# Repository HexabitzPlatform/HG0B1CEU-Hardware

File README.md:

# HG0B1CEU-Hardware
Hexabitz STM32G0B1CEU6N DevKit Hardware Design

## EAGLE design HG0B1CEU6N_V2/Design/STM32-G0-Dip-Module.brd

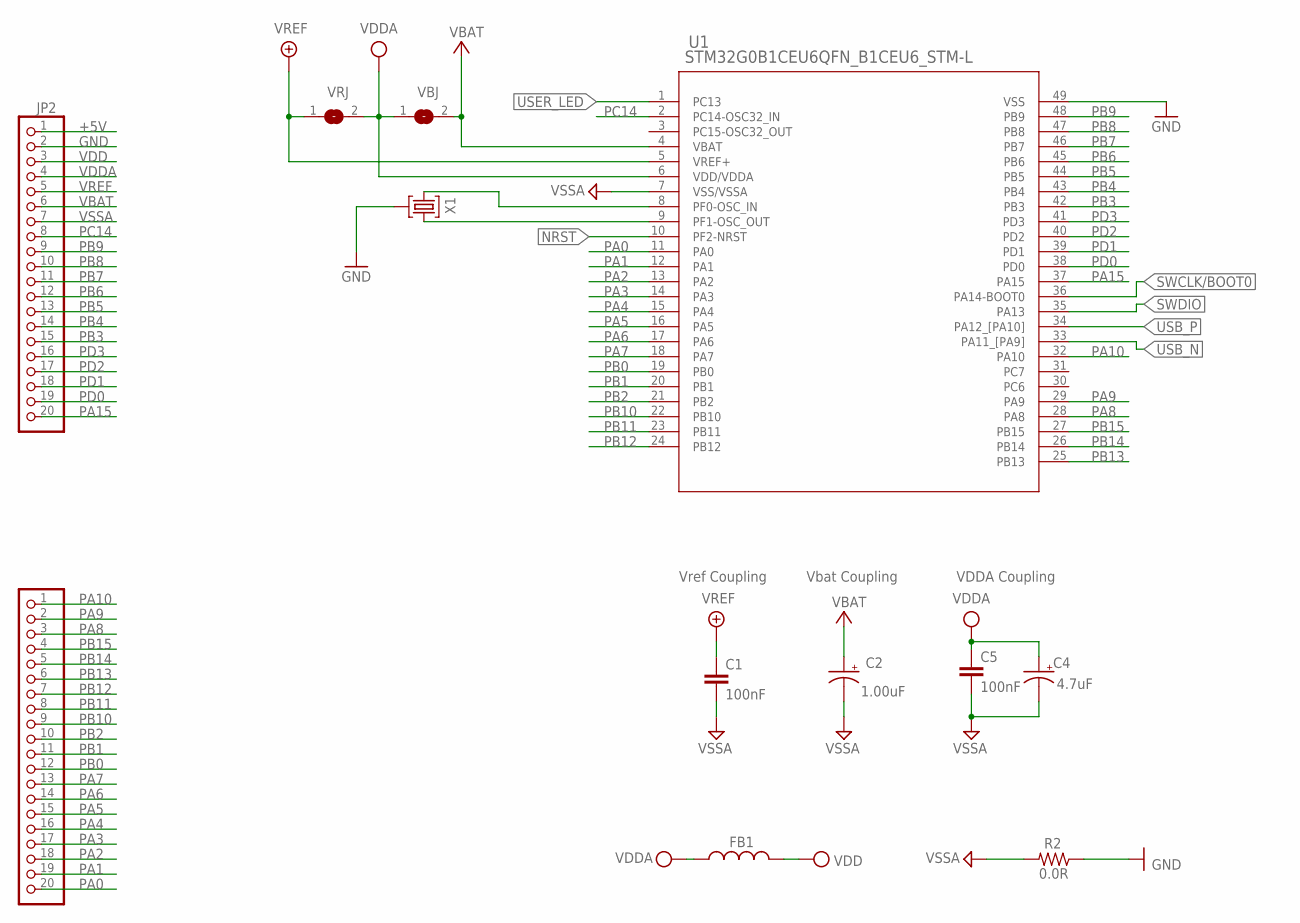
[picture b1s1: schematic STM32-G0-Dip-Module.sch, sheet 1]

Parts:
C1: 100nF; C-0603; TOLERANCE 10%; VOLTAGE_RATING 10V; MPN C0603C104K8RACTU
C2: 1.00uF; C-0805-POL; TOLERANCE 10%; VOLTAGE_RATING 16V; MPN CC0805KKX7R7BB105
C4: 4.7uF; C-0805-POL; TOLERANCE 10%; VOLTAGE_RATING 25V; MPN GRM21BC81E475KA12L
C5: 100nF; C-0603; TOLERANCE 10%; VOLTAGE_RATING 10; MPN C0603C104K8RACTU
FB1: FB-TDK_MMZ1608Y300B; MPN MMZ1608Y300B
JP1, JP2: PINHD-1X20; 1X20
R2: 0.0R; R-0603; MPN RC0603JR-070RL
U1: STM32G0B1CEU6QFN_B1CEU6_STM-L; QFN_B1CEU6_STM-L
VBJ: SJ
VRJ: SJ
X1: XTALL_CSTCE8M00G52

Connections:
+5V: JP2.1; also elsewhere on the board
CRYSTAL_N: U1.8 (PF0-OSC_IN), X1.P$1 (1)
CRYSTAL_P: U1.9 (PF1-OSC_OUT), X1.P$3 (3)
GND: JP2.2, R2.1, U1.49 (VSS), X1.P$2 (2); also elsewhere on the board
NRST: U1.10 (PF2-NRST); also elsewhere on the board
PA0: JP1.20, U1.11 (PA0)
PA1: JP1.19, U1.12 (PA1)
PA2: JP1.18, U1.13 (PA2)
PA3: JP1.17, U1.14 (PA3)
PA4: JP1.16, U1.15 (PA4)
PA5: JP1.15, U1.16 (PA5)
PA6: JP1.14, U1.17 (PA6)
PA7: JP1.13, U1.18 (PA7)
PA8: JP1.3, U1.28 (PA8)
PA9: JP1.2, U1.29 (PA9)
PA10: JP1.1, U1.32 (PA10)
PA15: JP2.20, U1.37 (PA15)
PB0: JP1.12, U1.19 (PB0)
PB1: JP1.11, U1.20 (PB1)
PB2: JP1.10, U1.21 (PB2)
PB3: JP2.15, U1.42 (PB3)
PB4: JP2.14, U1.43 (PB4)
PB5: JP2.13, U1.44 (PB5)
PB6: JP2.12, U1.45 (PB6)
PB7: JP2.11, U1.46 (PB7)
PB8: JP2.10, U1.47 (PB8)
PB9: JP2.9, U1.48 (PB9)
PB10: JP1.9, U1.22 (PB10)
PB11: JP1.8, U1.23 (PB11)
PB12: JP1.7, U1.24 (PB12)
PB13: JP1.6, U1.25 (PB13)
PB14: JP1.5, U1.26 (PB14)
PB15: JP1.4, U1.27 (PB15)
PC14: JP2.8, U1.2 (PC14-OSC32_IN)
PD0: JP2.19, U1.38 (PD0)
PD1: JP2.18, U1.39 (PD1)
PD2: JP2.17, U1.40 (PD2)
PD3: JP2.16, U1.41 (PD3)
SWCLK/BOOT0: U1.36 (PA14-BOOT0); also elsewhere on the board
SWDIO: U1.35 (PA13); also elsewhere on the board
USB_N: U1.33 (PA11_[PA9]); also elsewhere on the board
USB_P: U1.34 (PA12_[PA10]); also elsewhere on the board
USER_LED: U1.1 (PC13); also elsewhere on the board
VBAT: C2.1 (+), JP2.6, U1.4 (VBAT), VBJ.2
VDD: FB1.2, JP2.3; also elsewhere on the board
VDDA: C4.1 (+), C5.1, FB1.1, JP2.4, U1.6 (VDD/VDDA), VBJ.1, VRJ.2
VREF: C1.1, JP2.5, U1.5 (VREF+), VRJ.1
VSSA: C1.2, C2.2 (-), C4.2 (-), C5.2, JP2.7, R2.2, U1.7 (VSS/VSSA)

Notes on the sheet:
VDDA Coupling
Vref Coupling
Vbat Coupling

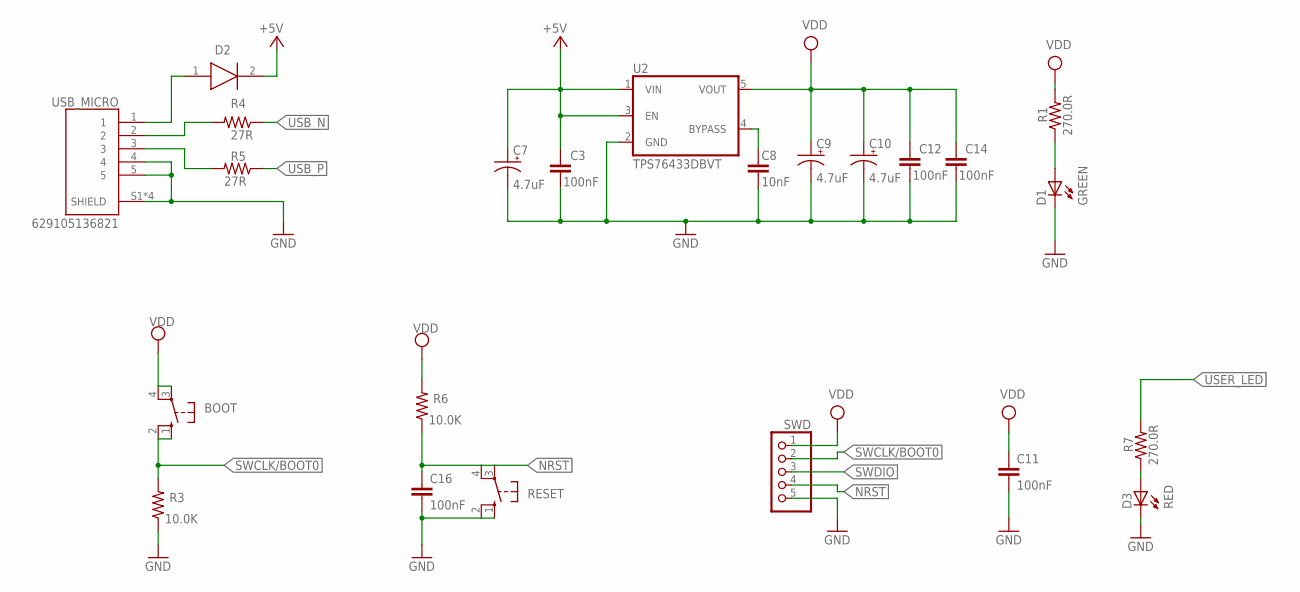
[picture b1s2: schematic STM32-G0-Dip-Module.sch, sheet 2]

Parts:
BOOT: 10-XX; B3F-10XX
C3, C12, C14: 100nF; C-0603; TOLERANCE 10%; VOLTAGE_RATING 10; MPN C0603C104K8RACTU
C7, C9, C10: 4.7uF; C-0805-POL; TOLERANCE 10%; VOLTAGE_RATING 25V; MPN GRM21BC81E475KA12L
C8: 10nF; C-0603; TOLERANCE 10%; VOLTAGE_RATING 10; MPN C0603C104K8RACTU
C11, C16: 100nF; C-0603; TOLERANCE 10%; VOLTAGE_RATING 10V; MPN C0603C104K8RACTU
D1: GREEN; VLMS1300-GS08; MPN VLMS1300-GS08
D2: FSM17PL-TP
D3: RED; VLMS1300-GS08; MPN VLMS1300-GS08
R1, R7: 270.0R; R-0603; TOLERANCE 1%; MPN RC0603FR-07270RL
R3, R6: 10.0K; R-0603; TOLERANCE 5%; MPN RC0603JR-0710KL
R4, R5: 27R; R-0603; TOLERANCE 5%; MPN RC0603JR-0710KL
RESET: 10-XX; B3F-10XX
SWD: PINHD-1X5/90; 1X05/90
U2: TPS76433DBVT; SOT25
USB_MICRO: 629105136821; WE_629105136821

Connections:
+5V: C3.1, C7.1 (+), D2.2 (K), U2.1 (VIN), U2.3 (EN); also elsewhere on the board
D_N: R4.2, USB_MICRO.2
D_P: R5.2, USB_MICRO.3
GND: C3.2, C7.2 (-), C8.2, C9.2 (-), C10.2 (-), C11.2, C12.2, C14.2, C16.2, D1.C, D3.C, R3.1, RESET.1 (S), RESET.2 (S1), SWD.5, U2.2 (GND), USB_MICRO.4, USB_MICRO.5, USB_MICRO.S1 (SHIELD), USB_MICRO.S2 (SHIELD), USB_MICRO.S3 (SHIELD), USB_MICRO.S4 (SHIELD); also elsewhere on the board
unnamed: D2.1 (A), USB_MICRO.1
unnamed: D3.A, R7.1
unnamed: D1.A, R1.1
unnamed: C8.1, U2.4 (BYPASS)
NRST: C16.1, R6.1, RESET.3, RESET.4 (P1), SWD.4; also elsewhere on the board
SWCLK/BOOT0: BOOT.1 (S), BOOT.2 (S1), R3.2, SWD.2; also elsewhere on the board
SWDIO: SWD.3; also elsewhere on the board
USB_N: R4.1; also elsewhere on the board
USB_P: R5.1; also elsewhere on the board
USER_LED: R7.2; also elsewhere on the board
VDD: BOOT.3, BOOT.4 (P1), C9.1 (+), C10.1 (+), C11.1, C12.1, C14.1, R1.2, R6.2, SWD.1, U2.5 (VOUT); also elsewhere on the board

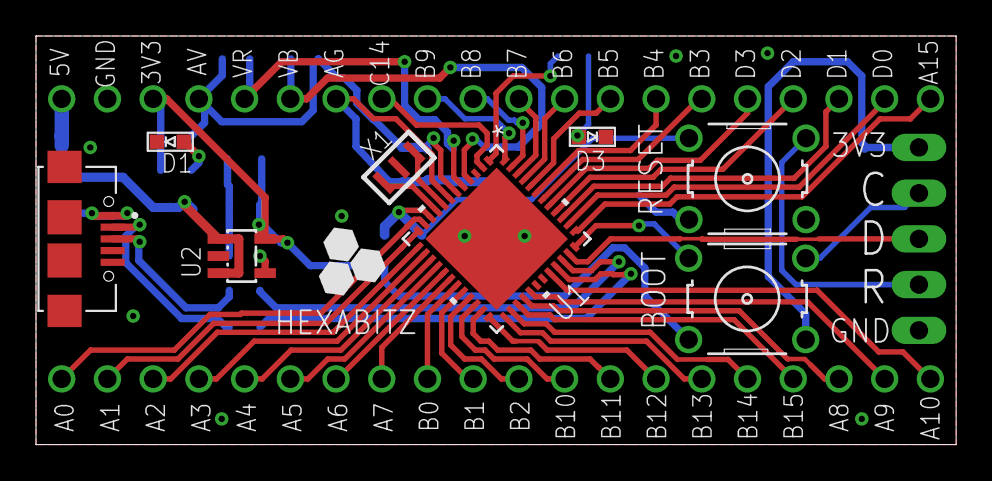
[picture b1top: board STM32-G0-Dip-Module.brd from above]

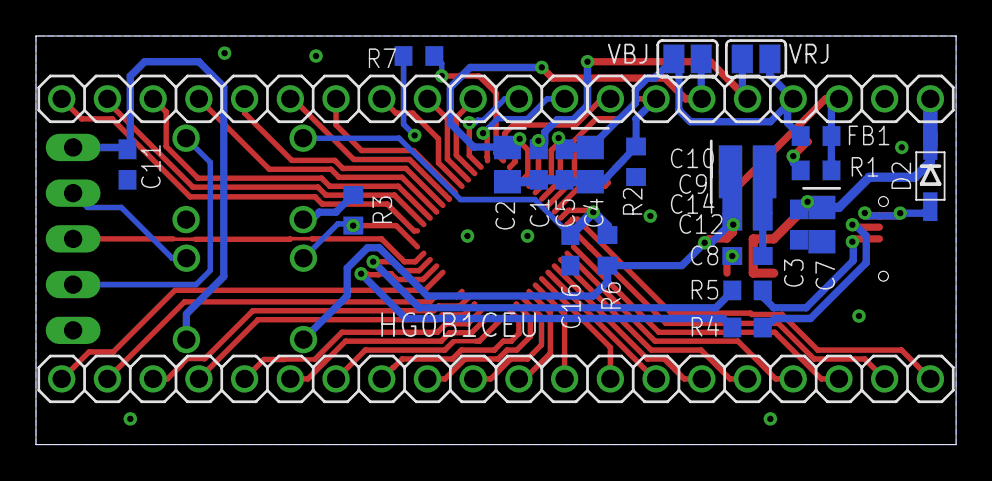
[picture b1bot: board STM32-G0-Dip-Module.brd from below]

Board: 2 copper layers, 51.1 x 22.7 mm, 35 parts (24 on the bottom side), 54 nets.

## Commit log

2022-08-19 Added .gitignore file
2022-08-23 Adding the Hardware Design files
2022-09-24 -Changing the Schematic design stile -Correcting some BOM-file data
2022-12-21 -Changing the electronic design and layout to improve the performance and ease of use
2022-12-28 -- Repairing some issues in the layout that related to keepout margins of the parts
2023-02-13 -Correcting some documentaion issues
2024-03-07 Fix documentation issue
2024-05-15 Update the BOM Standrize the files names

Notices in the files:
parts and their libraries:
HEXABITZ_ICs: COPYRIGHT: Copyright (C) 2022 Ultra Librarian. All rights reserved.
COPYRIGHT: Copyright (C) 2021 Ultra Librarian. All rights reserved.
